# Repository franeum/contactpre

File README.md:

# contactpre
preamplifier for a piezo contact mic (from alex rice project)

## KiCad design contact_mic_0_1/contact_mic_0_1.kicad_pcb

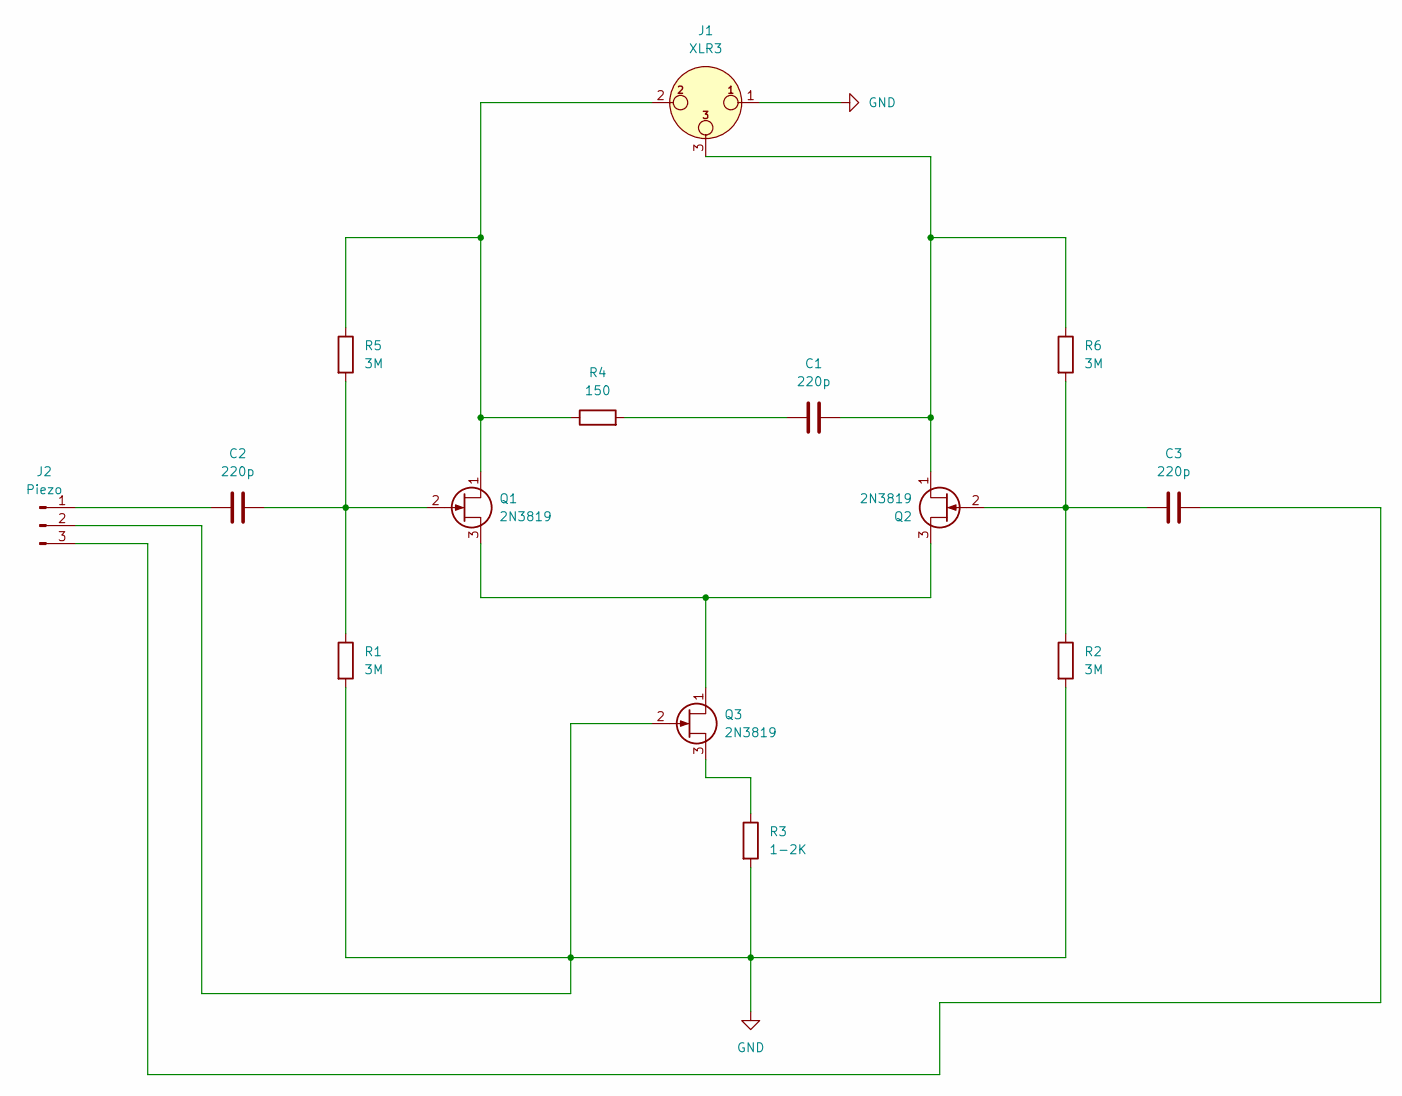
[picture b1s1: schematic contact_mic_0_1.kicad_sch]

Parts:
C1, C2, C3: 220p; C_Disc_D3.0mm_W1.6mm_P2.50mm
J1: XLR3; Jack_XLR_Neutrik_NC3MAAH_Horizontal
J2: Piezo; TE_826576-3_1x03_P3.96mm_Vertical
Q1, Q2, Q3: 2N3819; TO-92_Inline
R1, R2, R5, R6: 3M; R_Axial_DIN0207_L6.3mm_D2.5mm_P8.128mm_Horizontal
R3: 1-2K; R_Axial_DIN0207_L6.3mm_D2.5mm_P8.128mm_Horizontal
R4: 150; R_Axial_DIN0207_L6.3mm_D2.5mm_P8.128mm_Horizontal

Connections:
GND: J1.1, J2.2, Q3.2 (G), R1.2, R2.2, R3.2
unnamed: C1.1, R4.2
unnamed: C2.1, J2.1
unnamed: C3.2, J2.3
unnamed: J1.2, Q1.1 (D), R4.1, R5.1
unnamed: C2.2, Q1.2 (G), R1.1, R5.2
unnamed: Q1.3 (S), Q2.3 (S), Q3.1 (D)
unnamed: C1.2, J1.3, Q2.1 (D), R6.1
unnamed: C3.1, Q2.2 (G), R2.1, R6.2
unnamed: Q3.3 (S), R3.1

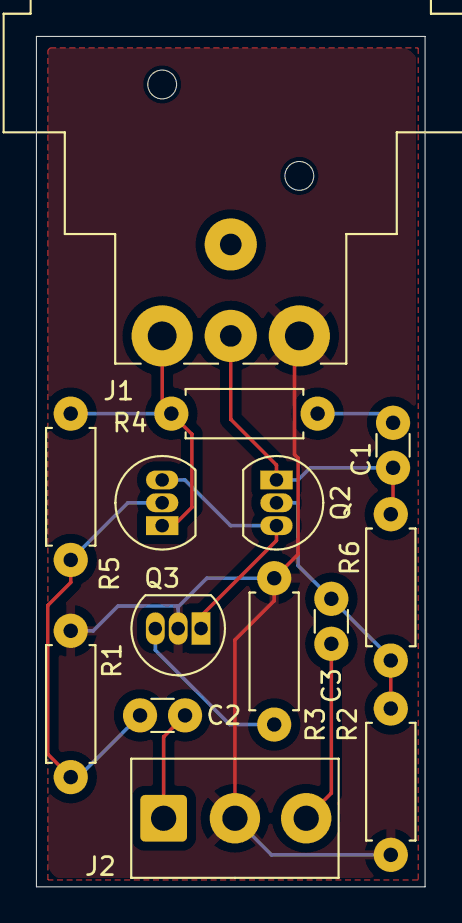
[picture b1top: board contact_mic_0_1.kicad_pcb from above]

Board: 2 copper layers, 21.6 x 47.2 mm, 14 parts (0 on the bottom side), 10 nets.
